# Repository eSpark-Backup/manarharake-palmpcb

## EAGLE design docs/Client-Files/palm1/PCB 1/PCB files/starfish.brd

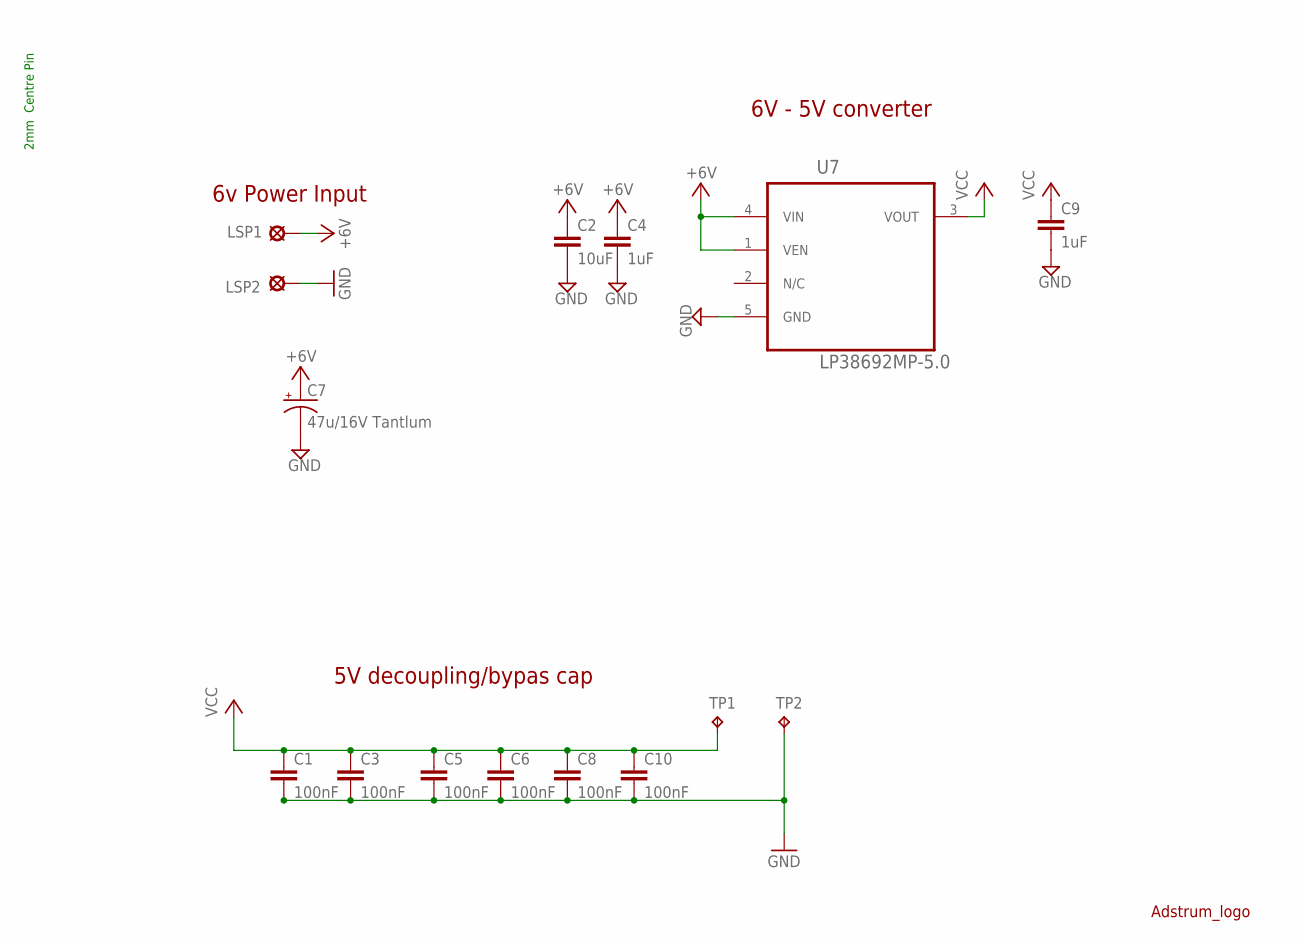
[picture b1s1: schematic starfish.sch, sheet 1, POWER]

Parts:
C1: 100nF; C1210
C2: 10uF; C0805
C3, C5, C6, C8, C10: 100nF; C0603
C4, C9: 1uF; C0805
C7: 47u/16V Tantlum; C/6032-28R
LSP1, LSP2: LSP10
TP1: vcc; B1,27
TP2: gnd; B1,27
U7: LP38692MP-5.0; SOT150P696X180-5N
U$16: ADSTRUM_LOGO

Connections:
+6V: C2.1, C4.1, C7.+, LSP1.MP, U7.1 (VEN), U7.4 (VIN); also elsewhere on the board
GND: C1.2, C2.2, C3.2, C4.2, C5.2, C6.2, C7.-, C8.2, C9.2, C10.2, LSP2.MP, TP2.TP, U7.5 (GND); also elsewhere on the board
VCC: C1.1, C3.1, C5.1, C6.1, C8.1, C9.1, C10.1, TP1.TP, U7.3 (VOUT); also elsewhere on the board

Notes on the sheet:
2mm Centre Pin
6V - 5V converter
5V decoupling/bypas cap
6v Power Input

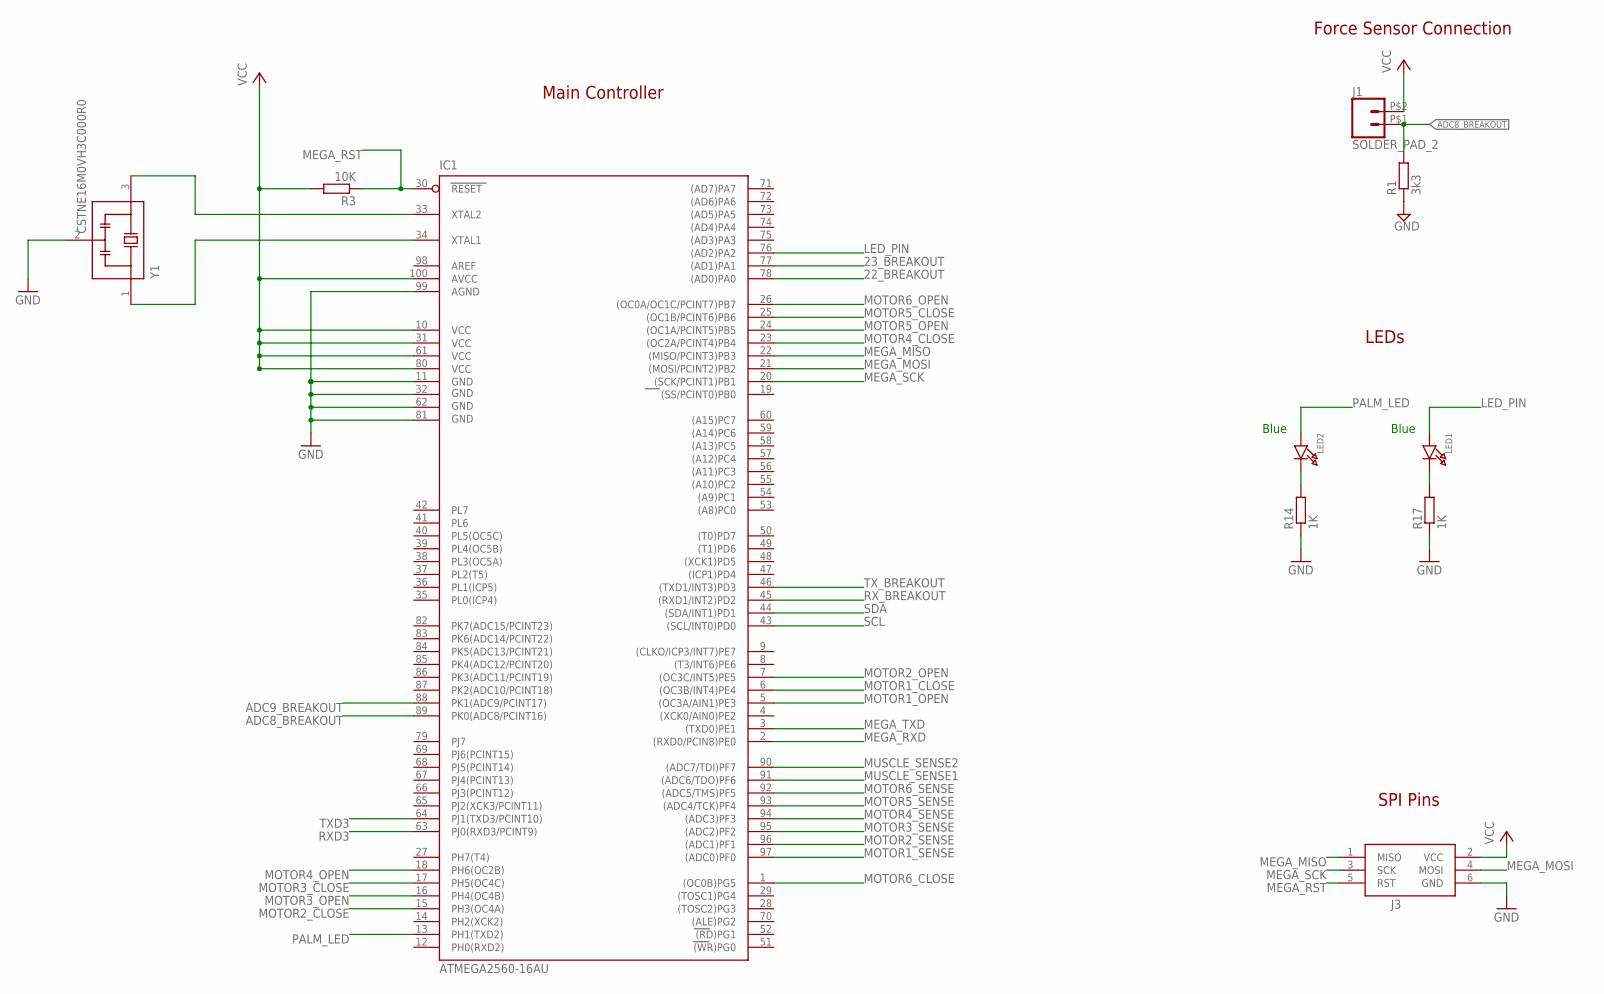
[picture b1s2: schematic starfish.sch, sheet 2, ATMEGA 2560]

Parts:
IC1: ATMEGA2560-16AU; TQFP100
J1: SOLDER_PAD_2
J3: DNF; AVRISP
LED1, LED2: LED0805; CHIPLED_0805
R1: 3k3; R0603
R3: 10K; R0603
R14, R17: 1K; R0603
Y1: CSTNE16M0VH3C000R0; OSC_CSTNE16M0VH3C000R0

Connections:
22_BREAKOUT: IC1.78 ((AD0)PA0)
23_BREAKOUT: IC1.77 ((AD1)PA1)
ADC8_BREAKOUT: IC1.89 (PK0(ADC8/PCINT16)), J1.P$1 (1), R1.2
ADC9_BREAKOUT: IC1.88 (PK1(ADC9/PCINT17))
GND: IC1.11 (GND), IC1.32 (GND1), IC1.62 (GND2), IC1.81 (GND3), IC1.99 (AGND), J3.6 (GND), R1.1, R14.1, R17.1, Y1.2 (GND); also elsewhere on the board
LED_PIN: IC1.76 ((AD2)PA2), LED1.A
MEGA_MISO: IC1.22 ((MISO/PCINT3)PB3), J3.1 (MISO)
MEGA_MOSI: IC1.21 ((MOSI/PCINT2)PB2), J3.4 (MOSI)
MEGA_RST: IC1.30 (RESET), J3.5 (RST), R3.1; also elsewhere on the board
MEGA_RXD: IC1.2 ((RXD0/PCIN8)PE0); also elsewhere on the board
MEGA_SCK: IC1.20 ((SCK/PCINT1)PB1), J3.3 (SCK)
MEGA_TXD: IC1.3 ((TXD0)PE1); also elsewhere on the board
MOTOR1_CLOSE: IC1.6 ((OC3B/INT4)PE4); also elsewhere on the board
MOTOR1_OPEN: IC1.5 ((OC3A/AIN1)PE3); also elsewhere on the board
MOTOR1_SENSE: IC1.97 ((ADC0)PF0); also elsewhere on the board
MOTOR2_CLOSE: IC1.15 (PH3(OC4A)); also elsewhere on the board
MOTOR2_OPEN: IC1.7 ((OC3C/INT5)PE5); also elsewhere on the board
MOTOR2_SENSE: IC1.96 ((ADC1)PF1); also elsewhere on the board
MOTOR3_CLOSE: IC1.17 (PH5(OC4C)); also elsewhere on the board
MOTOR3_OPEN: IC1.16 (PH4(OC4B)); also elsewhere on the board
MOTOR3_SENSE: IC1.95 ((ADC2)PF2); also elsewhere on the board
MOTOR4_CLOSE: IC1.23 ((OC2A/PCINT4)PB4); also elsewhere on the board
MOTOR4_OPEN: IC1.18 (PH6(OC2B)); also elsewhere on the board
MOTOR4_SENSE: IC1.94 ((ADC3)PF3); also elsewhere on the board
MOTOR5_CLOSE: IC1.25 ((OC1B/PCINT6)PB6); also elsewhere on the board
MOTOR5_OPEN: IC1.24 ((OC1A/PCINT5)PB5); also elsewhere on the board
MOTOR5_SENSE: IC1.93 ((ADC4/TCK)PF4); also elsewhere on the board
MOTOR6_CLOSE: IC1.1 ((OC0B)PG5); also elsewhere on the board
MOTOR6_OPEN: IC1.26 ((OC0A/OC1C/PCINT7)PB7); also elsewhere on the board
MOTOR6_SENSE: IC1.92 ((ADC5/TMS)PF5); also elsewhere on the board
MUSCLE_SENSE1: IC1.91 ((ADC6/TDO)PF6); also elsewhere on the board
MUSCLE_SENSE2: IC1.90 ((ADC7/TDI)PF7); also elsewhere on the board
unnamed: LED1.C, R17.2
unnamed: IC1.34 (XTAL1), Y1.1 (IN)
unnamed: LED2.C, R14.2
unnamed: IC1.33 (XTAL2), Y1.3 (OUT)
PALM_LED: IC1.13 (PH1(TXD2)), LED2.A
RXD3: IC1.63 (PJ0(RXD3/PCINT9)); also elsewhere on the board
RX_BREAKOUT: IC1.45 ((RXD1/INT2)PD2)
SCL: IC1.43 ((SCL/INT0)PD0); also elsewhere on the board
SDA: IC1.44 ((SDA/INT1)PD1); also elsewhere on the board
TXD3: IC1.64 (PJ1(TXD3/PCINT10)); also elsewhere on the board
TX_BREAKOUT: IC1.46 ((TXD1/INT3)PD3)
VCC: IC1.10 (VCC), IC1.31 (VCC1), IC1.61 (VCC2), IC1.80 (VCC3), IC1.100 (AVCC), J1.P$2 (2), J3.2 (VCC), R3.2; also elsewhere on the board

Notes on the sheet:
Blue
Force Sensor Connection
SPI Pins
LEDs
Main Controller

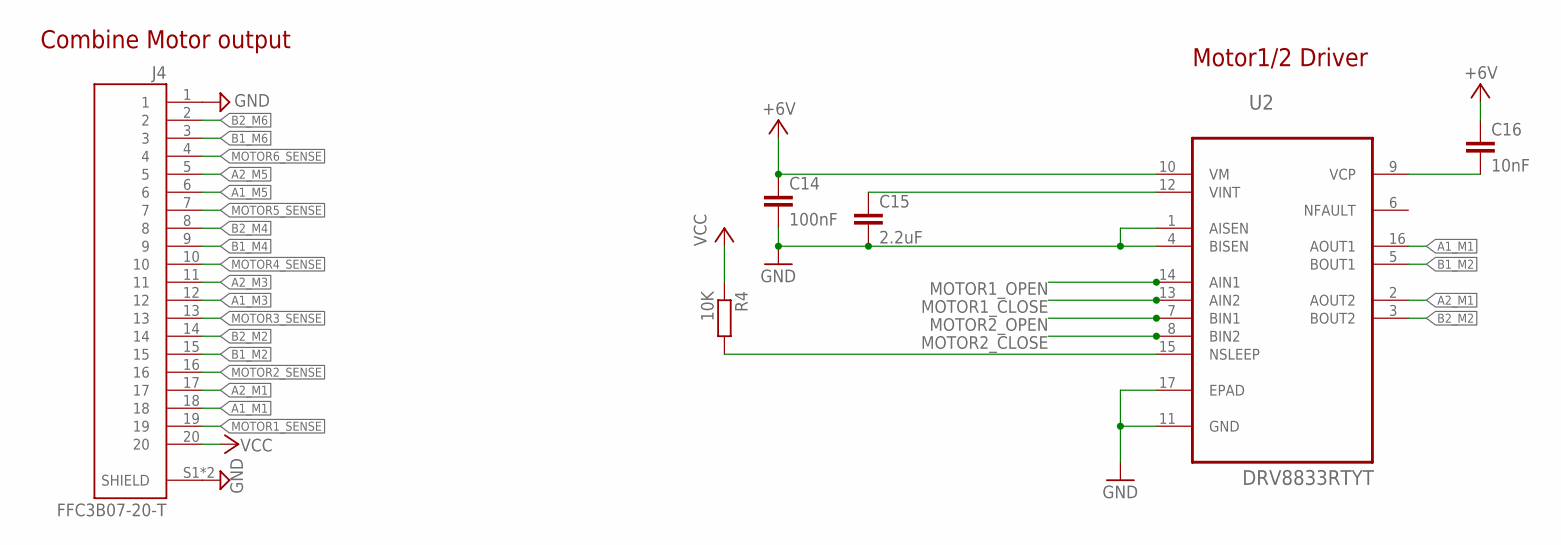
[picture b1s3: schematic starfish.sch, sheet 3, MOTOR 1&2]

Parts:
C14: 100nF; C0603
C15: 2.2uF; C0603
C16: 10nF; C0603
J4: FFC3B07-20-T; GCT_FFC3B07-20-T
R4: 10K; R0603
U2: DRV8833RTYT; QFN65P400X400X80-17N

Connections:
+6V: C14.1, C16.1, U2.10 (VM); also elsewhere on the board
A1_M1: J4.18, U2.16 (AOUT1)
A1_M3: J4.12; also elsewhere on the board
A1_M5: J4.6; also elsewhere on the board
A2_M1: J4.17, U2.2 (AOUT2)
A2_M3: J4.11; also elsewhere on the board
A2_M5: J4.5; also elsewhere on the board
B1_M2: J4.15, U2.5 (BOUT1)
B1_M4: J4.9; also elsewhere on the board
B1_M6: J4.3; also elsewhere on the board
B2_M2: J4.14, U2.3 (BOUT2)
B2_M4: J4.8; also elsewhere on the board
B2_M6: J4.2; also elsewhere on the board
GND: C14.2, C15.2, J4.1, J4.S1 (SHIELD), J4.S2 (SHIELD), U2.1 (AISEN), U2.4 (BISEN), U2.11 (GND), U2.17 (EPAD); also elsewhere on the board
MOTOR1_CLOSE: U2.13 (AIN2); also elsewhere on the board
MOTOR1_OPEN: U2.14 (AIN1); also elsewhere on the board
MOTOR1_SENSE: J4.19; also elsewhere on the board
MOTOR2_CLOSE: U2.8 (BIN2); also elsewhere on the board
MOTOR2_OPEN: U2.7 (BIN1); also elsewhere on the board
MOTOR2_SENSE: J4.16; also elsewhere on the board
MOTOR3_SENSE: J4.13; also elsewhere on the board
MOTOR4_SENSE: J4.10; also elsewhere on the board
MOTOR5_SENSE: J4.7; also elsewhere on the board
MOTOR6_SENSE: J4.4; also elsewhere on the board
unnamed: C16.2, U2.9 (VCP)
unnamed: R4.2, U2.15 (NSLEEP)
unnamed: C15.1, U2.12 (VINT)
VCC: J4.20, R4.1; also elsewhere on the board

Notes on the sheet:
Combine Motor output
Motor1/2 Driver

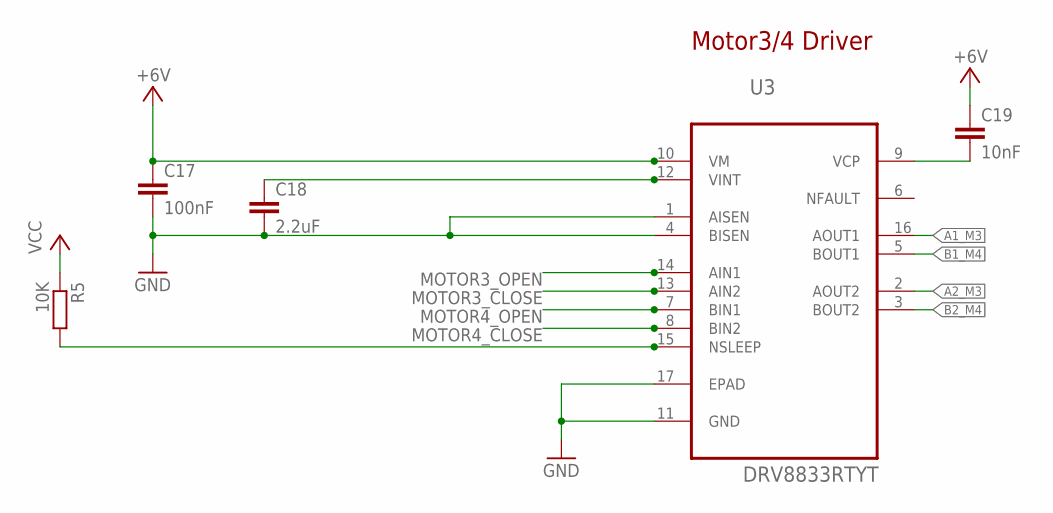
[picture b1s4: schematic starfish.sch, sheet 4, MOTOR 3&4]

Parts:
C17: 100nF; C0603
C18: 2.2uF; C0603
C19: 10nF; C0603
R5: 10K; R0603
U3: DRV8833RTYT; QFN65P400X400X80-17N

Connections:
+6V: C17.1, C19.1, U3.10 (VM); also elsewhere on the board
A1_M3: U3.16 (AOUT1); also elsewhere on the board
A2_M3: U3.2 (AOUT2); also elsewhere on the board
B1_M4: U3.5 (BOUT1); also elsewhere on the board
B2_M4: U3.3 (BOUT2); also elsewhere on the board
GND: C17.2, C18.2, U3.1 (AISEN), U3.4 (BISEN), U3.11 (GND), U3.17 (EPAD); also elsewhere on the board
MOTOR3_CLOSE: U3.13 (AIN2); also elsewhere on the board
MOTOR3_OPEN: U3.14 (AIN1); also elsewhere on the board
MOTOR4_CLOSE: U3.8 (BIN2); also elsewhere on the board
MOTOR4_OPEN: U3.7 (BIN1); also elsewhere on the board
unnamed: C19.2, U3.9 (VCP)
unnamed: C18.1, U3.12 (VINT)
unnamed: R5.2, U3.15 (NSLEEP)
VCC: R5.1; also elsewhere on the board

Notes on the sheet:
Motor3/4 Driver

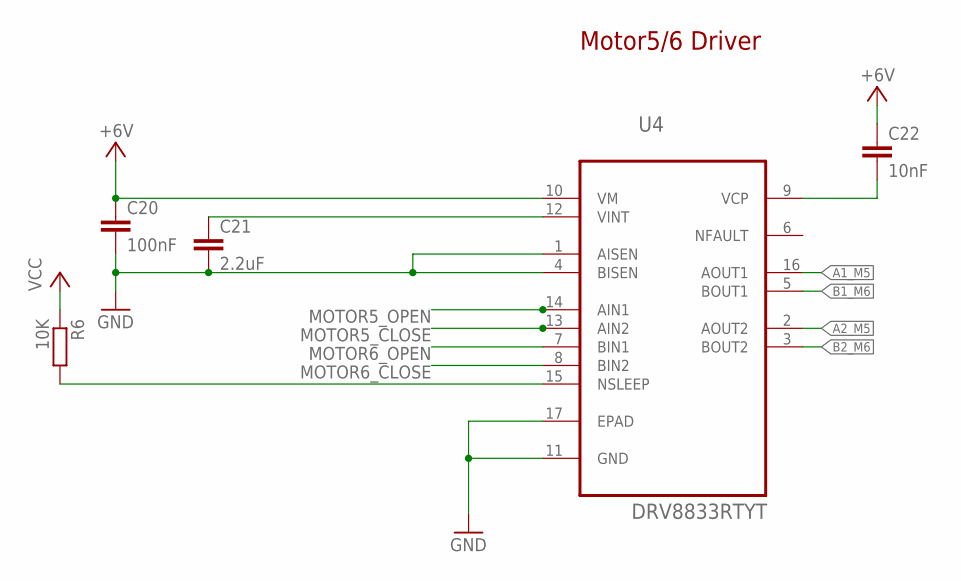
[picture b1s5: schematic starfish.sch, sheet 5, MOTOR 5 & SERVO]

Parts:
C20: 100nF; C0603
C21: 2.2uF; C0603
C22: 10nF; C0603
R6: 10K; R0603
U4: DRV8833RTYT; QFN65P400X400X80-17N

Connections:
+6V: C20.1, C22.1, U4.10 (VM); also elsewhere on the board
A1_M5: U4.16 (AOUT1); also elsewhere on the board
A2_M5: U4.2 (AOUT2); also elsewhere on the board
B1_M6: U4.5 (BOUT1); also elsewhere on the board
B2_M6: U4.3 (BOUT2); also elsewhere on the board
GND: C20.2, C21.2, U4.1 (AISEN), U4.4 (BISEN), U4.11 (GND), U4.17 (EPAD); also elsewhere on the board
MOTOR5_CLOSE: U4.13 (AIN2); also elsewhere on the board
MOTOR5_OPEN: U4.14 (AIN1); also elsewhere on the board
MOTOR6_CLOSE: U4.8 (BIN2); also elsewhere on the board
MOTOR6_OPEN: U4.7 (BIN1); also elsewhere on the board
unnamed: C21.1, U4.12 (VINT)
unnamed: C22.2, U4.9 (VCP)
unnamed: R6.2, U4.15 (NSLEEP)
VCC: R6.1; also elsewhere on the board

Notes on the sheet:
Motor5/6 Driver

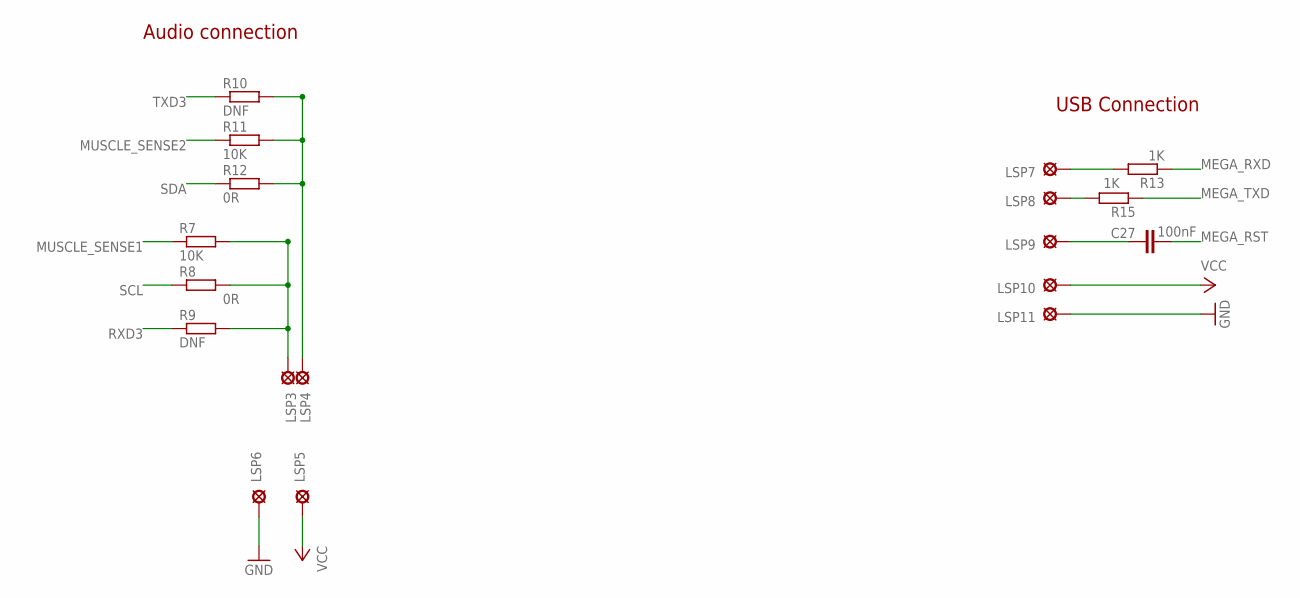
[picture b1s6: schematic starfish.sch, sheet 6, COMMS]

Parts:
C27: 100nF; C0603
LSP3, LSP4, LSP5, LSP6, LSP7, LSP8, LSP9, LSP10, LSP11: LSP10
R7, R11: 10K; R0603
R8, R12: 0R; R0603
R9, R10: DNF; R0603
R13, R15: 1K; R0603

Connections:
GND: LSP6.MP, LSP11.MP; also elsewhere on the board
MEGA_RST: C27.2; also elsewhere on the board
MEGA_RXD: R13.1; also elsewhere on the board
MEGA_TXD: R15.1; also elsewhere on the board
MUSCLE_SENSE1: R7.1; also elsewhere on the board
MUSCLE_SENSE2: R11.1; also elsewhere on the board
unnamed: LSP4.MP, R10.2, R11.2, R12.2
unnamed: C27.1, LSP9.MP
unnamed: LSP3.MP, R7.2, R8.2, R9.2
unnamed: LSP7.MP, R13.2
unnamed: LSP8.MP, R15.2
RXD3: R9.1; also elsewhere on the board
SCL: R8.1; also elsewhere on the board
SDA: R12.1; also elsewhere on the board
TXD3: R10.1; also elsewhere on the board
VCC: LSP5.MP, LSP10.MP; also elsewhere on the board

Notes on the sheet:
Audio connection
USB Connection

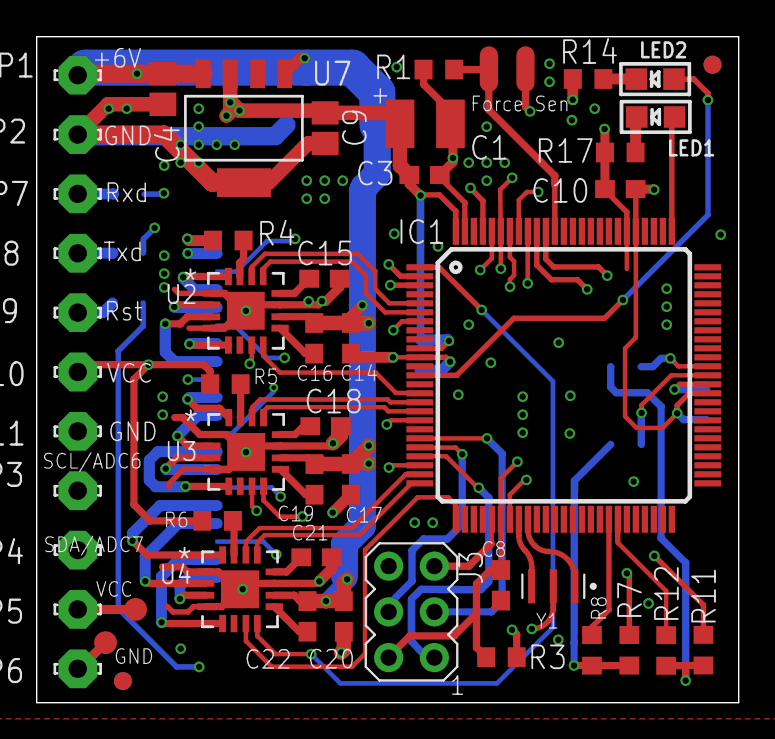
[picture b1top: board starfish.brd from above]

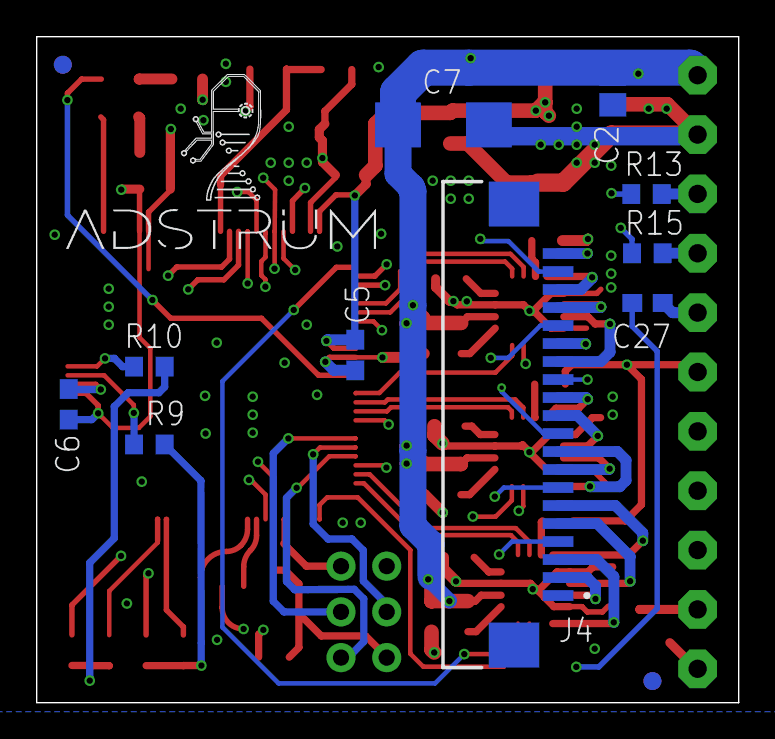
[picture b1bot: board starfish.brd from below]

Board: 4 copper layers, 39.0 x 37.0 mm, 62 parts (11 on the bottom side), 66 nets.

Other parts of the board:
U$1, U$17: CIRCLE-1MM-2R

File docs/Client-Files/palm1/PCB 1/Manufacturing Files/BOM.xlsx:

Starfish PCB BOM |  | Created By: Dharmik Patel https://www.upwork.com/o/profiles/users/~01178b3bf7c1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
Qty | Value | Part no | Make | Package | Parts | Description
1 | 100nF - 50V | CC1210KKX7R9BB104 | Yageo | C1210 | C1 | CAPACITOR
9 | 100nF - 50V | CC0603KRX7R9BB104 | Yageo | C0603 | C3, C5, C6, C8, C10, C14, C17, C20, C27 | CAPACITOR
3 | 10nF - 50V | CL10B103KB8WPJC | Samsung Electro-Mechanics | C0603 | C16, C19, C22 | CAPACITOR
1 | 10uF | GRM21BR61H106KE43L | Murata Electronics | C0805 | C2 | CAPACITOR
2 | 1uF | CC0805KKX7R9BB105 | Yageo | C0805 | C4, C9 | CAPACITOR
3 | 2.2uF | GRM188R61H225KE11D | Murata Electronics | C0603 | C15, C18, C21 | CAPACITOR
1 | 47u/16V Tantlum | TAJC476K016RNJ | AVX | C/6032-28R | C7 | POLARIZED CAPACITOR
4 | 1K | RC0603FR-071KL | Yageo | R0603 | R13, R14, R15, R17 | RESISTOR
1 | 3k3 | M55342K12B3E30MTSV-ND |  | R0603 | R1 | RESISTOR
2 | DNF | R-EU_R0603 |  | R0603 | R9, R10 | RESISTOR
2 | 0R | R-EU_R0603 |  | R0603 | R8, R12 | RESISTOR
6 | 10K | RC0603FR-0710KL | Yageo | R0603 | R3, R4, R5, R6, R7, R11 | RESISTOR
1 | ATMEGA2560-16AU | ATMEGA2560-16AU |  | TQFP100 | IC1 | MICROCONTROLLER
1 | CSTNE16M0VH3C000R0 | CSTNE16M0VH3C000R0 |  | OSC_CSTNE16M0VH3C000R0 | Y1 | 16MHz Ceramic Resonator Built in Capacitor 15pF Â±0.15% 40 Ohms
1 | DNF | AVRISP-6 |  | AVRISP | J3 | AVR ISP HEADER
3 | DRV8833RTYT | DRV8833RTYT |  | QFN65P400X400X80-17N | U2, U3, U4 | DUAL H-BRIDGE MOTOR DRIVER,QFN-16
1 | FFC3B07-20-T | FFC3B07-20-T |  | GCT_FFC3B07-20-T | J4 | FPC 1.0mm Pitch, Side entry, Top contact, SMT, Height 2.5mm, Slide type
1 | LP38692MP-5.0 | LP38692MP-5.0 |  | SOT150P696X180-5N | U7 | Linear Regulator Check availability

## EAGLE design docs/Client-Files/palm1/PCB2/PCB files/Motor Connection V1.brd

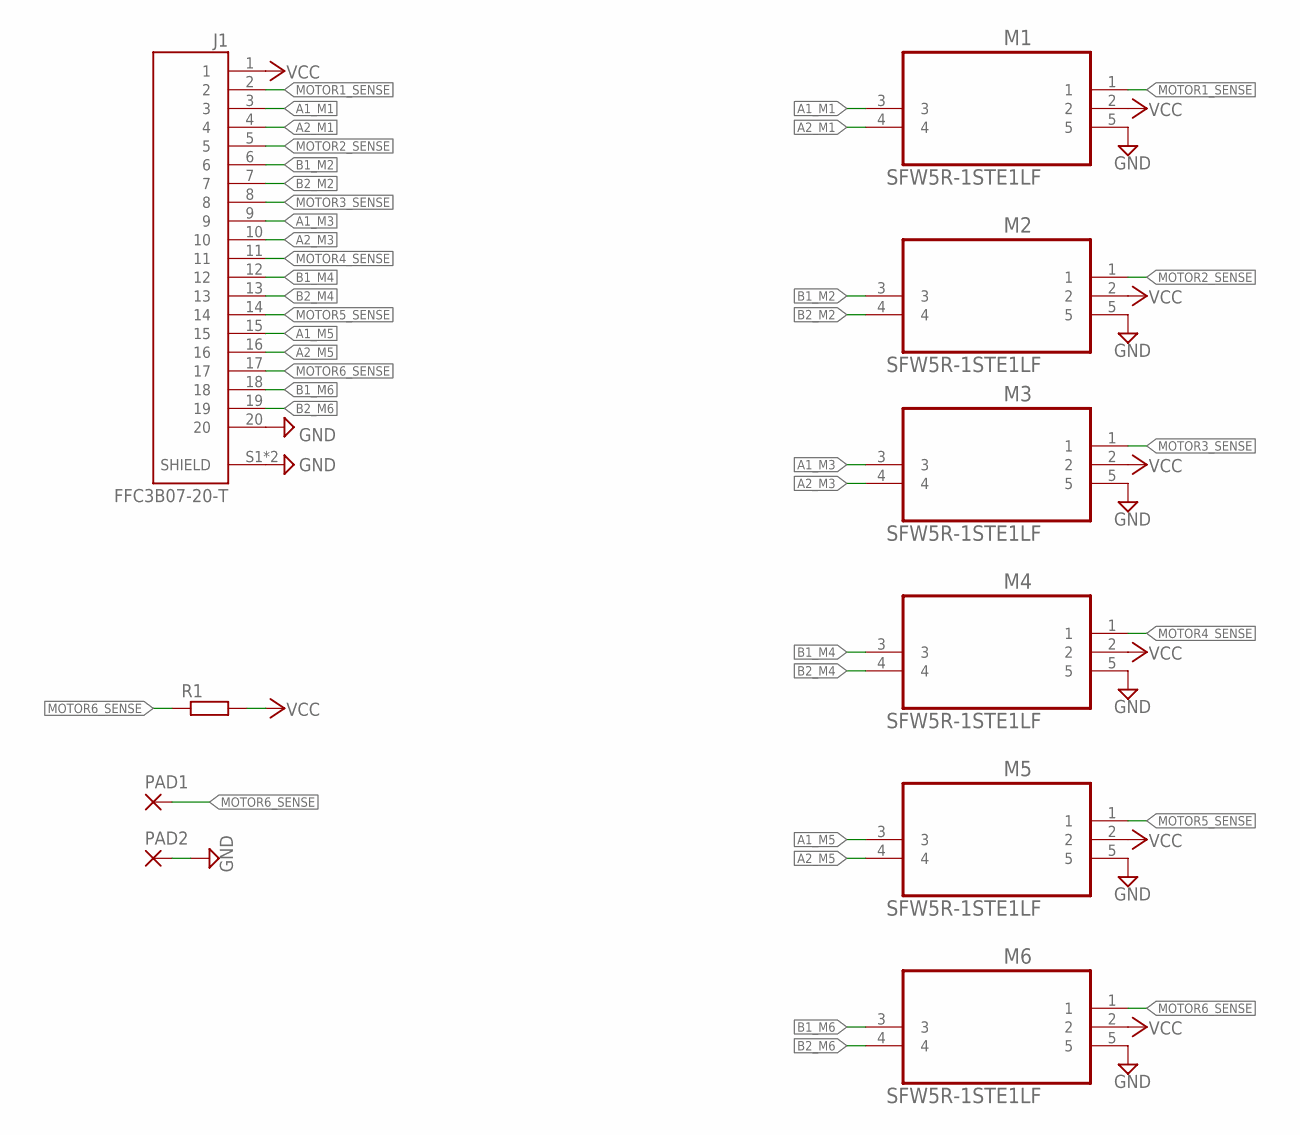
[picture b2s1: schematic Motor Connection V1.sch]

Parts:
J1: FFC3B07-20-T; GCT_FFC3B07-20-T
M1, M2, M3, M4, M5, M6: SFW5R-1STE1LF; FCI_SFW5R-1STE1LF
PAD1, PAD2: SMD2; SMD1,27-2,54
R1: R-EU_R0603; R0603

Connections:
A1_M1: J1.3, M1.3
A1_M3: J1.9, M3.3
A1_M5: J1.15, M5.3
A2_M1: J1.4, M1.4
A2_M3: J1.10, M3.4
A2_M5: J1.16, M5.4
B1_M2: J1.6, M2.3
B1_M4: J1.12, M4.3
B1_M6: J1.18, M6.3
B2_M2: J1.7, M2.4
B2_M4: J1.13, M4.4
B2_M6: J1.19, M6.4
GND: J1.20, J1.S1 (SHIELD), J1.S2 (SHIELD), M1.5, M2.5, M3.5, M4.5, M5.5, M6.5, PAD2.1
MOTOR1_SENSE: J1.2, M1.1
MOTOR2_SENSE: J1.5, M2.1
MOTOR3_SENSE: J1.8, M3.1
MOTOR4_SENSE: J1.11, M4.1
MOTOR5_SENSE: J1.14, M5.1
MOTOR6_SENSE: J1.17, M6.1, PAD1.1, R1.1
VCC: J1.1, M1.2, M2.2, M3.2, M4.2, M5.2, M6.2, R1.2

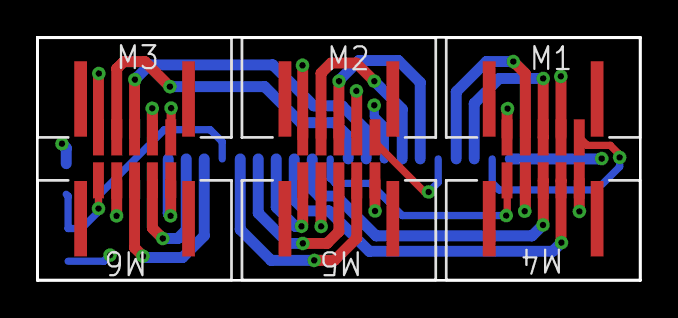
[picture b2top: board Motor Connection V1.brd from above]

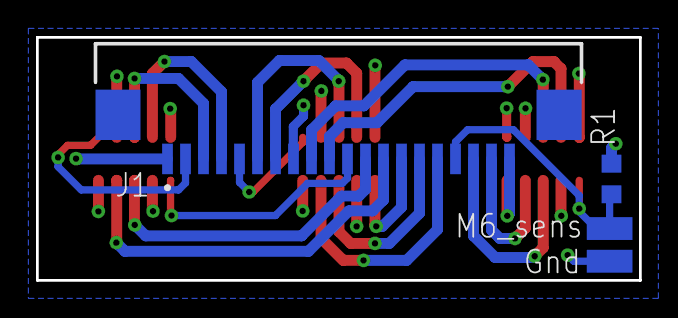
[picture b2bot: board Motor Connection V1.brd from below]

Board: 4 copper layers, 33.5 x 13.5 mm, 10 parts (4 on the bottom side), 20 nets.

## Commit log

2024-06-12 client files and gitignore pushed
2024-06-12 step file uploaded
2024-06-12 #1 In-progress.
2024-06-13 #1 Schematic In-progress:
2024-06-13 #1 Schematic Completed: Parts placement in-progress.
2024-06-14 #1 Schematic completed: PDF Generated: Client BOM Generated.
2024-06-14 #1 Updated PDF.
2024-06-14 #1 Parts updated in Schematic: Fresh BOM generated.
2024-06-14 #1 JLCPCB and Client BOM generated.
2024-06-14 #1 Parts placement in-progress.
2024-06-15 #1 PCB designing in-progress.
2024-06-15 #1 Routing In-progress
2024-06-16 #1 Routing in-progress.
2024-06-16 #1 Footprint updated: Routing In-progress:
2024-06-18 #1 BOM's updated with FPC Part No. : Re-routing in-progress.
2024-06-18 #1 Re-routing in-progress.
2024-06-19 #1 Done: Fresh Deliverables generated: BOM Updated with changes.
2024-06-20 #1 @MarsVirgo Client and JLCPCB BOM Updated.
2024-06-20 pcb reference dxf and step files added
2024-06-20 #1 Changes in Schematic done: Changes in PCB In-progress.
2024-06-20 #1 Connector update in Client and JLCPCB BOM.
2024-06-20 #1 PCB Size Reduced: Routing In-progress.
2024-06-21 #1 Fresh PDF Generated.
2024-06-21 #1 PCB Completed: Fresh Deliverables generated.
2024-06-26 #1 Updated Gerber Files.
2024-06-26 #1 Updated Gerber and Pick n Place files.
2024-09-19 #3 Schematic changes done PCB updated Deliverables generated and BOM updated with C29 cap.
2024-11-14 #4 Order Placement Complete.
2025-01-13 #5 Changes Update and Fresh Deliverables Generated.
2025-01-13 #5 Version Name update.
2025-04-23 #5 Serial pins on test points net label change to hardware TX0 RX0. PDF updated
2025-04-24 #5 Completed and Deliverables generated
2025-04-30 #5 In progress
2025-05-05 #5 Routing in progress
2025-05-06 #5 Routing completed
2025-05-07 #5 Completed Deliverables and BOM generated
2025-05-07 #5 Gerbers and NC drill files added

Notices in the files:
parts and their libraries:
microbuilder: This work is placed in the public domain, and may be freely used for commercial and non-commercial work with the following conditions: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
SparkFun-Connectors: Licensing: Creative Commons ShareAlike 4.0 International - https://creativecommons.org/licenses/by-sa/4.0
